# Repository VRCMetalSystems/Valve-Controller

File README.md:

# Valve-Controller
Repo for the PCB files for the Valve controller

# Instructions for ordering

## Required Files
All the required files can be found in ./OrderFiles/
1. CAMFILES.zip
2. WhiteJewel-all-pos.csv
3. WhiteJewel.csv

# Steps
0. Download/clone this repo and extract it if needed.
1. Go to [JLCPCB.com](https://cart.jlcpcb.com/quote?orderType=1&stencilWidth=100&stencilLength=100&stencilCounts=5&stencilLayer=2&stencilPly=1.6&steelmeshSellingPriceRecordNum=A8256537-5522-491C-965C-646F5842AEC9&purchaseNumber=)
2. Click on ***Add your gerber file***
3. Navigate to OrderFiles/CAMFILES.zip and upload it to the site. Wait till you see a preview of the board.
   - You can also drag and drop
4. Select the number of boards to be ordered in the ***PCB Qty*** text box.
    - You can order >50 boards but the assembly process has max of 50.
5. Make sure the ***Remove Order Number*** is set to ***YES***. 
6. Click on the ***SMT Assembly*** slider.
7. Click on ***Assemble Top side*** radio button to choose Top side assembly.
8. Accept the terms and conditions and click ***Confirm***
9. Upload the BOM and the CPL files in the appropriate spots
    - BOM file is called *WhiteJewel.csv*
    - CPL file is called *WhiteJewel-all-pos.csv*
10. Click Next 
11. If everything is processed successfully, The site will ask to confirm what parts to be placed. D5 and D6 are optional and can be removed by
clinking the trash can icon
12. After the cliking Next, the site will show you what it thnks the Assembled PCB will look like. 
    - Note that the site often gets the rotation of the parts wrong on the render. This is not indicative of the final board and is not an issue
13. Click on ***Save to cart*** to add the order to cart. 
14. Get a the credit card from the Purchasing department, Apply any "Coupons" that the site lets you and complete the order.
15. In addition, the following parts will have to be ordered via Digikey
      - 1x  377-1807-ND per board
      - 2x  609-3940-ND per board

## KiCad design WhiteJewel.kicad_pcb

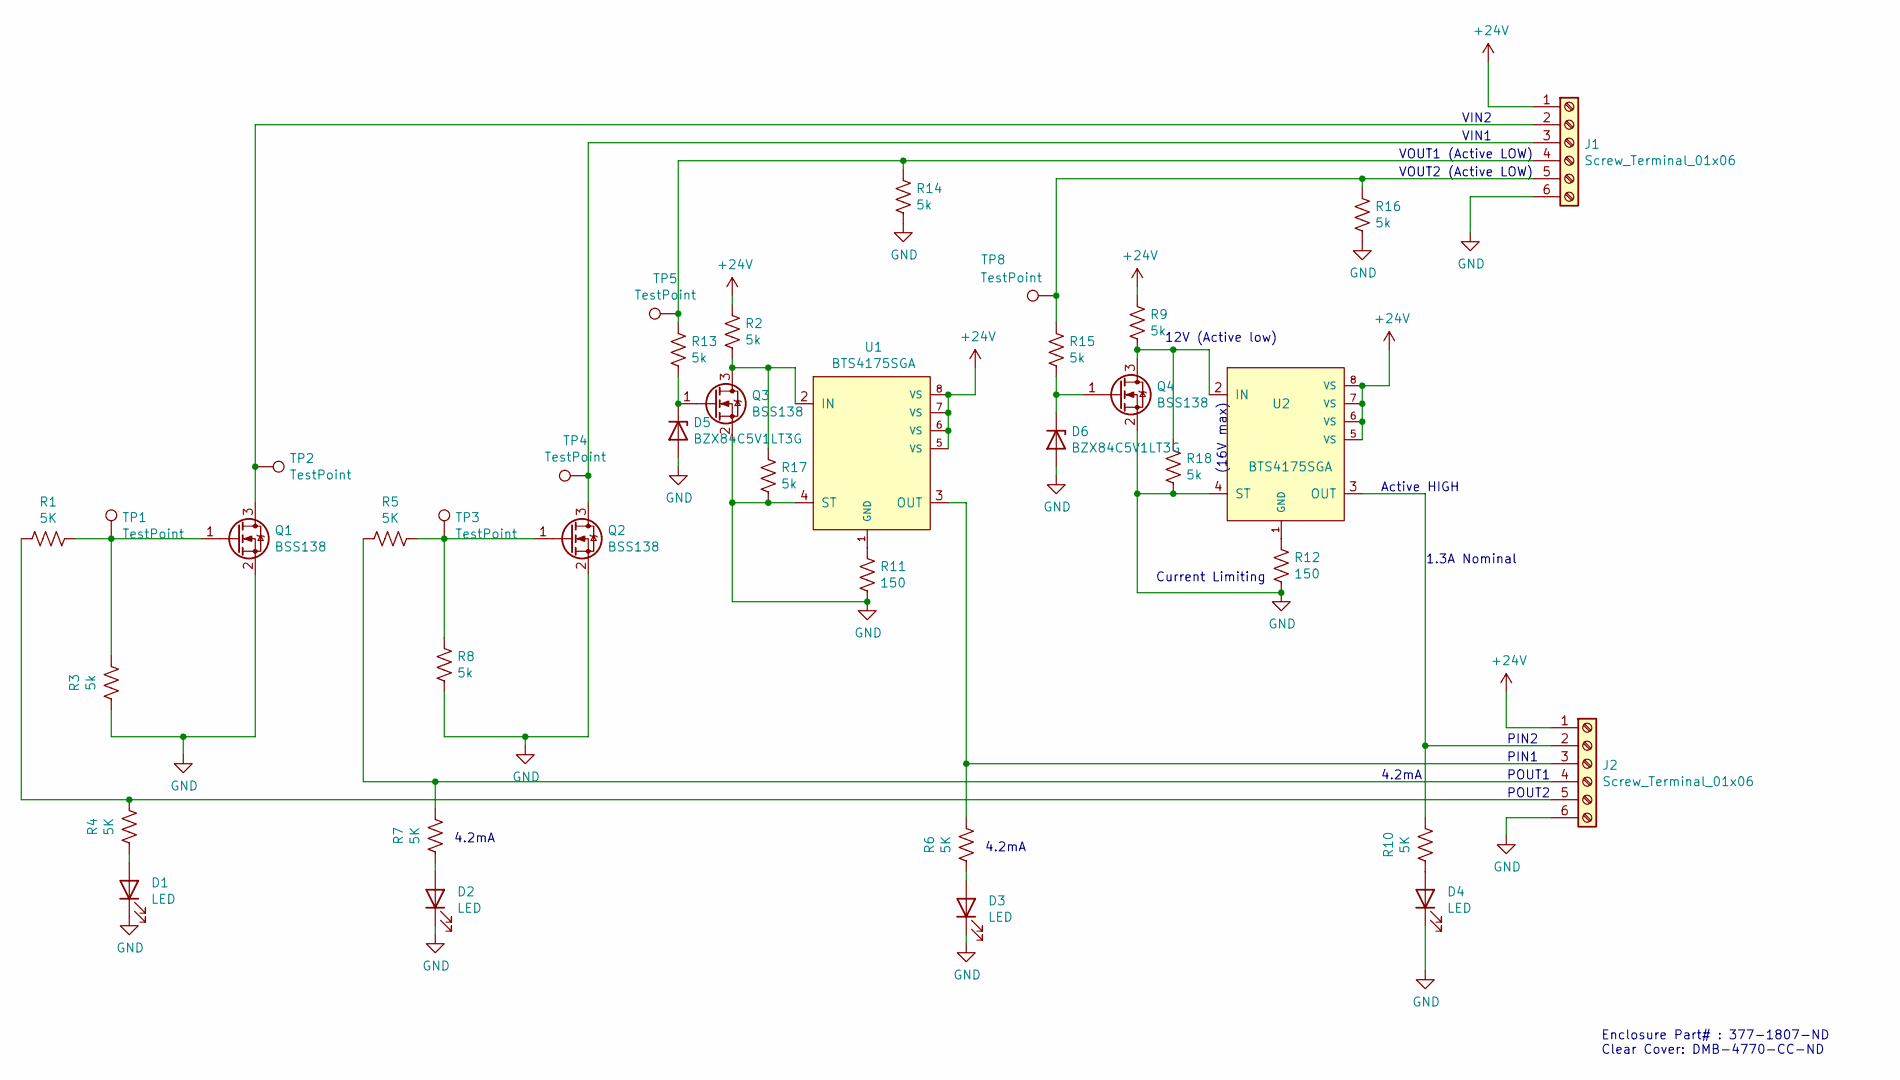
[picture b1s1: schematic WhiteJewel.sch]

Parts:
D1, D2, D3, D4: LED; D_0805_2012Metric_Pad1.15x1.40mm_HandSolder; LCSC C63855
D5: ‎BZX84C5V1LT3G; D_SOT-23_ANK
D6: BZX84C5V1LT3G; D_SOT-23_ANK
J1, J2: Screw_Terminal_01x06; TerminalBlock_bornier-6_P5.08mm; Digikey 609-3940-ND
Q1, Q2, Q3, Q4: BSS138; SOT-23; LCSC C82045
R1, R4, R5, R6, R7, R10: 5K; R_0805_2012Metric_Pad1.15x1.40mm_HandSolder; LCSC C78980
R2, R3, R8, R9, R13, R14, R15, R16, R17, R18: 5k; R_0805_2012Metric_Pad1.15x1.40mm_HandSolder; LCSC C78980
R11, R12: 150; R_0805_2012Metric_Pad1.15x1.40mm_HandSolder; LCSC C17471
TP1, TP2, TP3, TP4, TP5, TP8: TestPoint; TestPoint_Pad_D2.5mm
U1, U2: BTS4175SGA; Infineon_PG-DSO-8-27_3.9x4.9mm_EP2.65x3mm; LCSC C152451

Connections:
+24V: J1.1, J2.1, R2.1, R9.1, U1.5 (VS), U1.6 (VS), U1.7 (VS), U1.8 (VS), U2.5 (VS), U2.6 (VS), U2.7 (VS), U2.8 (VS)
GND: D1.1 (K), D2.1 (K), D3.1 (K), D4.1 (K), D5.2 (A), D6.2 (A), J1.6, J2.6, Q1.2 (S), Q2.2 (S), Q3.2 (S), Q4.2 (S), R3.2, R8.2, R11.2, R12.2, R14.2, R16.2, R17.2, R18.2, U1.4 (ST), U2.4 (ST)
unnamed: D1.2 (A), R4.2
unnamed: D2.2 (A), R7.2
unnamed: D3.2 (A), R6.2
unnamed: D4.2 (A), R10.2
unnamed: D5.1 (K), Q3.1 (G), R13.2
unnamed: D6.1 (K), Q4.1 (G), R15.2
unnamed: J1.2, Q1.3 (D), TP2.1
unnamed: J1.3, Q2.3 (D), TP4.1
unnamed: J1.4, R13.1, R14.1, TP5.1
unnamed: J1.5, R15.1, R16.1, TP8.1
unnamed: J2.2, R10.1, U2.3 (OUT)
unnamed: J2.3, R6.1, U1.3 (OUT)
unnamed: J2.4, R5.2, R7.1
unnamed: J2.5, R1.2, R4.1
unnamed: Q1.1 (G), R1.1, R3.1, TP1.1
unnamed: Q2.1 (G), R5.1, R8.1, TP3.1
unnamed: Q3.3 (D), R2.2, R17.1, U1.2 (IN)
unnamed: Q4.3 (D), R9.2, R18.1, U2.2 (IN)
unnamed: R11.1, U1.1 (GND)
unnamed: R12.1, U2.1 (GND)

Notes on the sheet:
4.2mA
1.3A Nominal
VIN2
VIN1
VOUT1 (Active LOW)
VOUT2 (Active LOW)
PIN2
PIN1
POUT1
POUT2
Current Limiting
12V (Active low)
(16V max)
Active HIGH
Enclosure Part# : 377-1807-ND‎ Clear Cover: DMB-4770-CC-ND

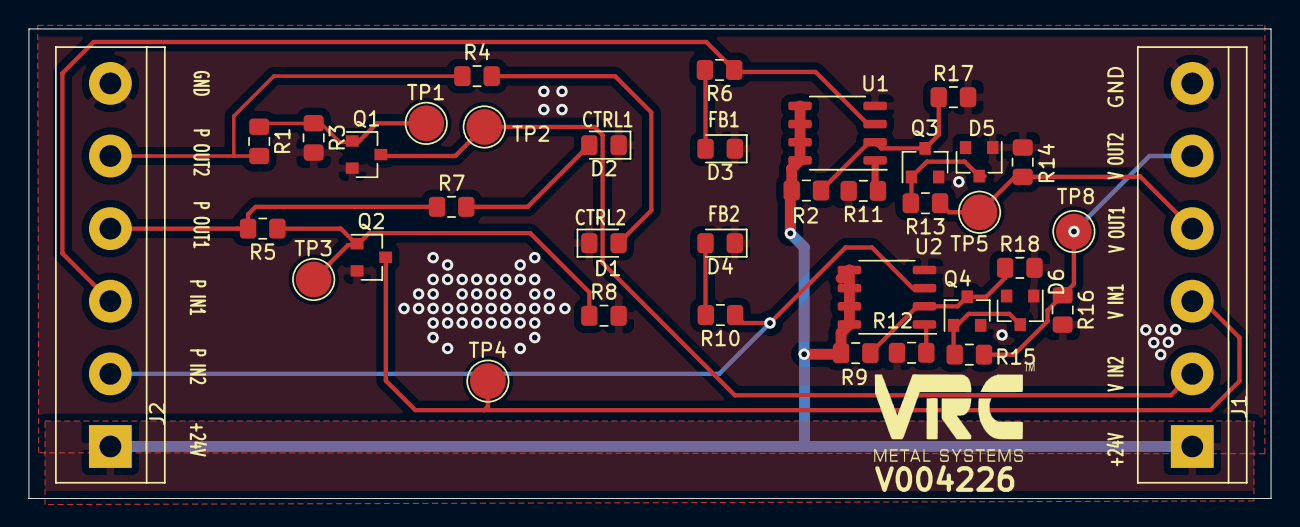
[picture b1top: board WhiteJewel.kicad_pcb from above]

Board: 2 copper layers, 86.9 x 32.9 mm, 39 parts (0 on the bottom side), 22 nets.

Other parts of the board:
LG1: Logo; VRCLogo

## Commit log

2021-01-04 Ported files over from personal repo
2021-01-04 Added PDFs for easy reference
2021-01-04 Added README with instructions for ordering
2021-01-04 Added seperate folder for ordering
2021-01-05 Added Enclosure and Terminal block part numbers
2021-01-07 Added zip file
